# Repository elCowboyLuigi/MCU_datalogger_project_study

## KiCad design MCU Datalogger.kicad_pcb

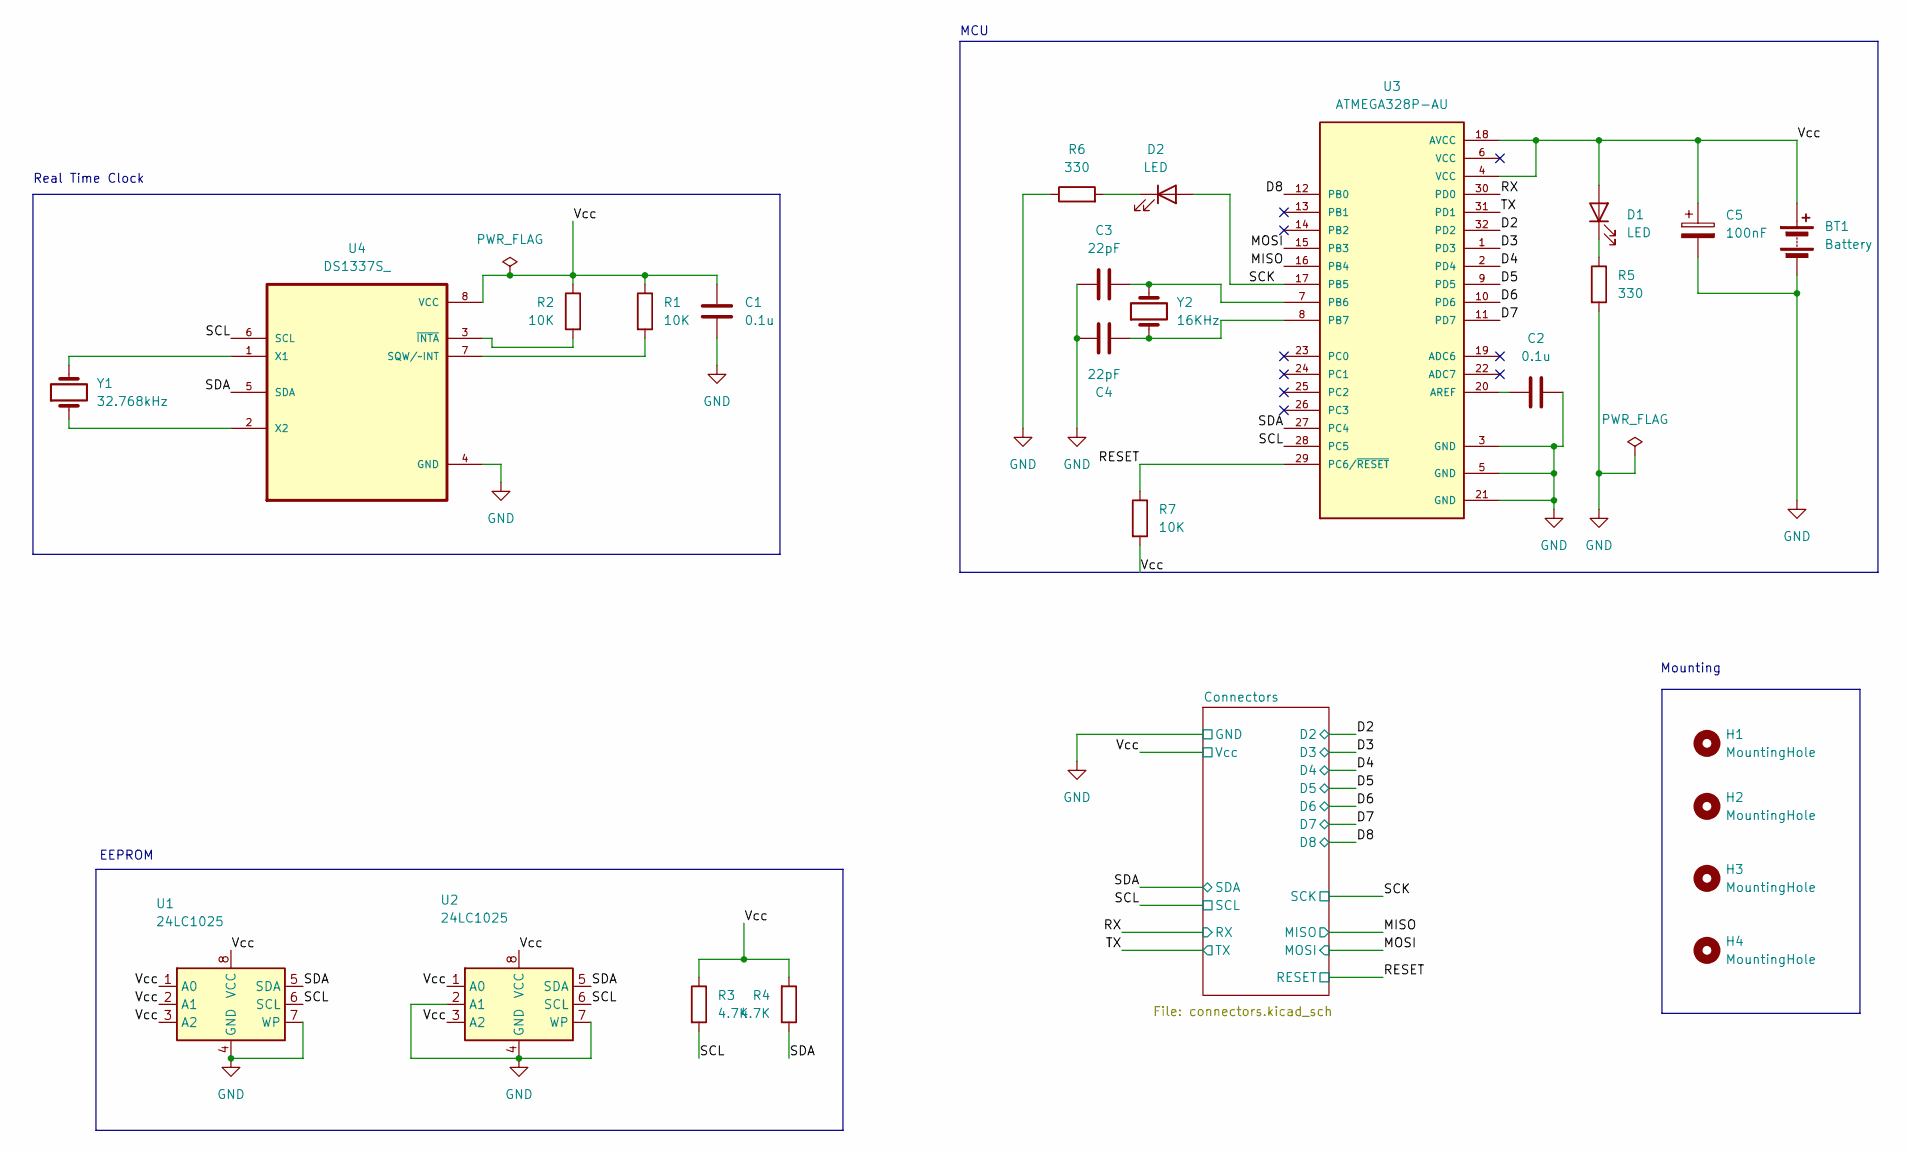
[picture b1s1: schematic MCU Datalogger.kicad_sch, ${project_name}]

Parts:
BT1: Battery; PinHeader_1x02_P2.54mm_Vertical
C1, C2: 0.1u; C_0805_2012Metric_Pad1.18x1.45mm_HandSolder
C3, C4: 22pF; C_0805_2012Metric_Pad1.18x1.45mm_HandSolder
C5: 100nF; C_0805_2012Metric_Pad1.18x1.45mm_HandSolder
D1, D2: LED; LED_0805_2012Metric_Pad1.15x1.40mm_HandSolder
H1, H2, H3, H4: MountingHole; MountingHole_2.1mm
R1, R2, R7: 10K; R_0805_2012Metric_Pad1.20x1.40mm_HandSolder
R3, R4: 4.7K; R_0805_2012Metric_Pad1.20x1.40mm_HandSolder
R5, R6: 330; R_0805_2012Metric_Pad1.20x1.40mm_HandSolder
U1, U2: 24LC1025; SOIC-8_5.275x5.275mm_P1.27mm
U3: ATMEGA328P-AU; QFP80P900X900X120-32N; PARTREV 8271A
U4: DS1337S_; SOIC127P600X175-8N
Y1: 32.768kHz; Crystal_SMD_5032-2Pin_5.0x3.2mm_HandSoldering
Y2: 16KHz; Crystal_SMD_5032-2Pin_5.0x3.2mm_HandSoldering

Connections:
/D2: U3.32 (PD2); also elsewhere on the board
/D3: U3.1 (PD3); also elsewhere on the board
/D4: U3.2 (PD4); also elsewhere on the board
/D5: U3.9 (PD5); also elsewhere on the board
/D6: U3.10 (PD6); also elsewhere on the board
/D7: U3.11 (PD7); also elsewhere on the board
/D8: U3.12 (PB0); also elsewhere on the board
/MISO: U3.16 (PB4); also elsewhere on the board
/MOSI: U3.15 (PB3); also elsewhere on the board
/RESET: R7.1, U3.29 (PC6/~RESET); also elsewhere on the board
/RX: U3.30 (PD0); also elsewhere on the board
/SCK: D2.2 (A), U3.17 (PB5); also elsewhere on the board
/SCL: R3.2, U1.6 (SCL), U2.6 (SCL), U3.28 (PC5), U4.6 (SCL); also elsewhere on the board
/SDA: R4.1, U1.5 (SDA), U2.5 (SDA), U3.27 (PC4), U4.5 (SDA); also elsewhere on the board
/TX: U3.31 (PD1); also elsewhere on the board
/Vcc: BT1.1 (+), C1.1, C5.1, D1.2 (A), R1.1, R2.1, R3.1, R4.2, R7.2, U1.1 (A0), U1.2 (A1), U1.3 (A2), U1.8 (VCC), U2.1 (A0), U2.3 (A2), U2.8 (VCC), U3.4 (VCC), U3.18 (AVCC), U4.8 (VCC); also elsewhere on the board
GND: BT1.2 (-), C1.2, C2.2, C3.1, C4.2, C5.2, R5.2, R6.1, U1.4 (GND), U1.7 (WP), U2.2 (A1), U2.4 (GND), U2.7 (WP), U3.3 (GND), U3.5 (GND), U3.21 (GND), U4.4 (GND); also elsewhere on the board
unnamed: D1.1 (K), R5.1
unnamed: D2.1 (K), R6.2
unnamed: C2.1, U3.20 (AREF)
unnamed: C3.2, U3.7 (PB6), Y2.2
unnamed: C4.1, U3.8 (PB7), Y2.1
unnamed: R1.2, U4.7 (SQW/~INT)
unnamed: U4.1 (X1), Y1.2
unnamed: U4.2 (X2), Y1.1
unnamed: R2.2, U4.3 (~INTA)

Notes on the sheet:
MCU
EEPROM
Real Time Clock
Mounting

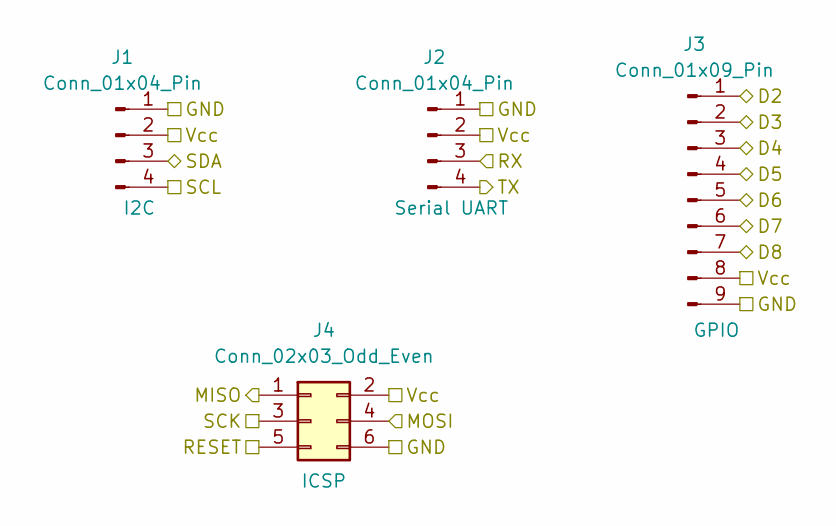
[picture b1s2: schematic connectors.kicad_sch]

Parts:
J1, J2: Conn_01x04_Pin; PinHeader_1x04_P2.54mm_Vertical
J3: Conn_01x09_Pin; PinHeader_1x09_P2.54mm_Vertical
J4: Conn_02x03_Odd_Even; PinHeader_2x03_P2.54mm_Vertical

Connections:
/D2: J3.1; also elsewhere on the board
/D3: J3.2; also elsewhere on the board
/D4: J3.3; also elsewhere on the board
/D5: J3.4; also elsewhere on the board
/D6: J3.5; also elsewhere on the board
/D7: J3.6; also elsewhere on the board
/D8: J3.7; also elsewhere on the board
/MISO: J4.1; also elsewhere on the board
/MOSI: J4.4; also elsewhere on the board
/RESET: J4.5; also elsewhere on the board
/RX: J2.3; also elsewhere on the board
/SCK: J4.3; also elsewhere on the board
/SCL: J1.4; also elsewhere on the board
/SDA: J1.3; also elsewhere on the board
/TX: J2.4; also elsewhere on the board
/Vcc: J1.2, J2.2, J3.8, J4.2; also elsewhere on the board
GND: J1.1, J2.1, J3.9, J4.6; also elsewhere on the board

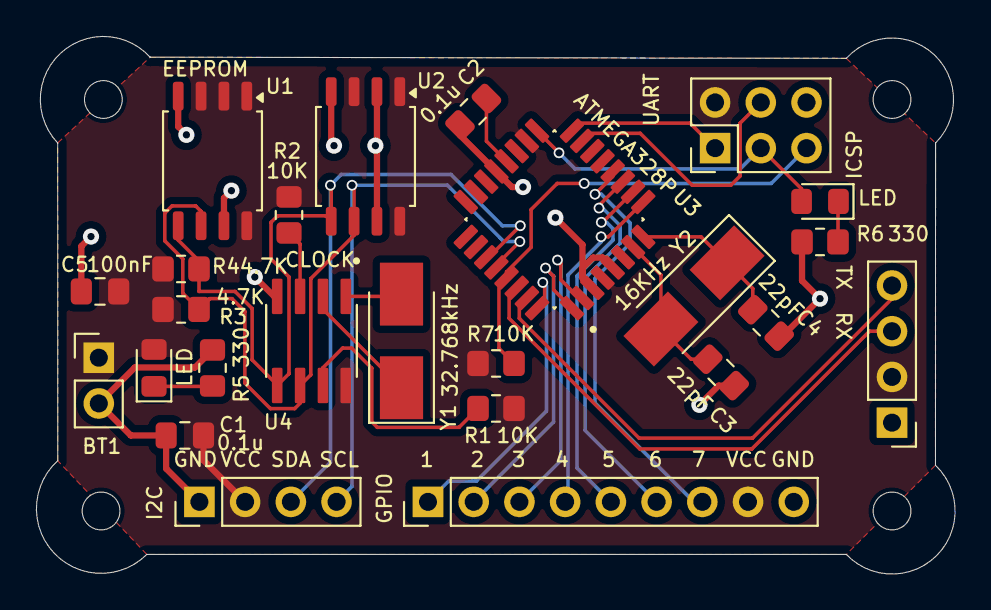
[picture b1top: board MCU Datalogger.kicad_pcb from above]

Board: 2 copper layers, 51.0 x 29.9 mm, 29 parts (0 on the bottom side), 26 nets.

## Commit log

2024-09-30 first commit.
2024-09-30 add a new resistor
2024-09-30 new branch with new capacitor
2024-09-30 edited a few resistors
2024-10-02 latest edit
2024-10-03 all symbols were added to the schematic
2024-10-03 updating the project with all necessary component libraries
2024-10-03 added values to the components
2024-10-03 proceeded to wire all the components on the first sheet
2024-10-04 the sheet is fully wired ready for an ERC
2024-10-04 the net classes were set up and the schematic was properly labeled
2024-10-04 new branch created for a 2 layer PCB design
2024-10-04 fixed gitignore patterns
2024-10-04 commited the placement of components
2024-10-07 completed the routing of the PCB
2024-10-07 fixed some issues with the EEPROM footprint 3d models
2024-10-07 finished the 2 layer PCB project
2024-10-07 modified routing and added a ground plane to the board
2024-10-08 fixed .gitignore rules
2024-10-08 starterd the layout editing
2024-10-08 finished the layout of the 4 layer PCB, still needs to finish silkscreen layer and review for any bugs
2024-10-09 finished the development of the 4 layer PCB, next step is to do a review on the design
2024-10-09 fixed some fill zones issues
2024-10-09 fixed two bugs on the schematic related to the clock wiring
2024-10-09 modified .gitignore
2024-10-09 set .gitattributes rules
2024-10-09 rerouted the PCB after aplyed fixes to the schematics related to the clock circutits
2024-10-09 merged changes to the schematics
2024-10-09 finished routing the fixes to the 2 layer PCB
2024-10-11 started routing layout
2024-10-11 finished an improved version of the 2 layer PCB
